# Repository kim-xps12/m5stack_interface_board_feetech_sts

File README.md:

# Feetech STS interface board for M5Stack

## About
M5StackからFeetech STSシリーズのシリアルサーボを操作するためのオリジナル基板です．KiCAD 7で設計しました．FE-URT-1([秋月リンク](https://akizukidenshi.com/catalog/g/gM-16295/))のUART機能のみを取り出して実装したため，同基板と比較して小型に収まっています．

## Appearance
**組み立て前**

**完成品**

## Usage
配線と動作の様子はこちら．
https://www.youtube.com/watch?v=_5FpvqL4ExI

動作確認用にM5Stack向けのサンプルコードをm5stack_uart_feetech_stsのリポジトリ（[リンク
](https://github.com/kim-xps12/m5stack_uart_feetech_sts/)）にて公開しています．よろしければご利用ください．

## schematics

## BOM
| Symbol | Model Number |URL, Values|
| --- | --- | --- |
| Q1  | 2SA1162GR<br> | [https://akizukidenshi.com/catalog/g/gI-02702/](https://akizukidenshi.com/catalog/g/gI-02702/)<br> |
| U1  | MAX3485ED<br> | [https://akizukidenshi.com/catalog/g/gI-16211/](https://akizukidenshi.com/catalog/g/gI-16211/)<br> |
| U2  | AP7333<br> | [https://akizukidenshi.com/catalog/g/gI-11360/](https://akizukidenshi.com/catalog/g/gI-11360/)<br> |
| J1  | JST B4B-PH-K-S(LF)(SN) | [https://www.sengoku.co.jp/mod/sgk\_cart/detail.php?code=4DK2-SDDB](https://www.sengoku.co.jp/mod/sgk_cart/detail.php?code=4DK2-SDDB)<br> |
| J2  | JST B2B-XH-A(LF)(SN) | [https://akizukidenshi.com/catalog/g/gC-12247/](https://akizukidenshi.com/catalog/g/gC-12247/)<br> |
| J3  | Molex 5267-03A-X | [https://www.sengoku.co.jp/mod/sgk\_cart/detail.php?code=EEHD-0HWA](https://www.sengoku.co.jp/mod/sgk_cart/detail.php?code=EEHD-0HWA)<br> |
| R   | 0608 inch / 1608 jis metric | R1=7.5k, R2=20k, R3=R4=2.2k |
| C   | 0608 inch / 1608 jis metric | C1=0.1 u, C2=C3=1u |

## Distribution
本基板（部品未実装）はboothで頒布中です．よろしければご利用ください．
https://b-sky-lab.booth.pm/items/5083992

## Reference
Feetechインターフェースボード回路図
https://akizukidenshi.com/download/ds/akizuki/feetech_digital_servo_20220729.pdf

## Disclaimer
MITライセンスでの公開です．本設計および頒布した基板において生じた一切の損害等について作者は責任を負いません．予めご了承ください．

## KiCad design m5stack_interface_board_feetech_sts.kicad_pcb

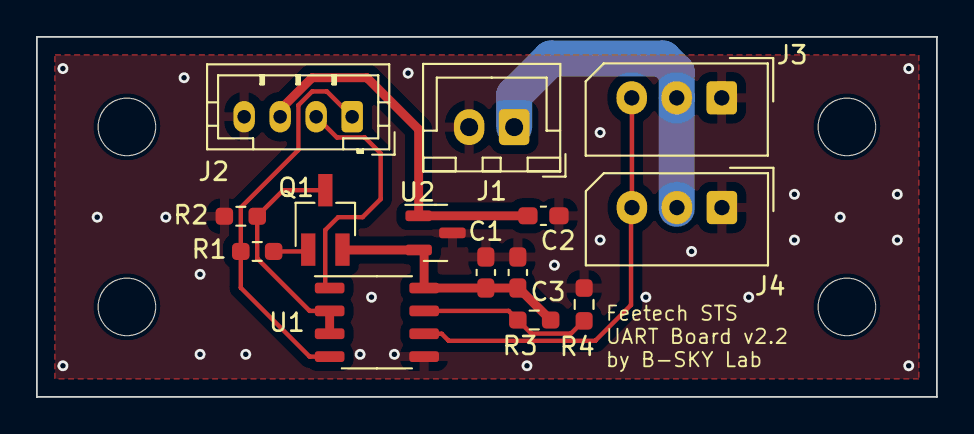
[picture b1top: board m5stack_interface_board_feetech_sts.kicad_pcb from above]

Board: 2 copper layers, 50.0 x 20.0 mm, 18 parts (0 on the bottom side), 10 nets.

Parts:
C1: 0.1u; C_0603_1608Metric_Pad1.08x0.95mm_HandSolder
C2, C3: 1u; C_0603_1608Metric_Pad1.08x0.95mm_HandSolder
J1: B2B-XH-A(LF)(SN); JST_XH_B2B-XH-A_1x02_P2.50mm_Vertical
J2: B4B-PH-K-S(LF)(SN); JST_PH_B4B-PH-K_1x04_P2.00mm_Vertical
J3, J4: 22035035; Molex_SPOX_5267-03A_1x03_P2.50mm_Vertical
MH1, MH2, MH3, MH4: MountingHole_3.2mm_M3
Q1: 2SA1162GR; SC-59_Handsoldering
R1: 7.5k; R_0603_1608Metric_Pad0.98x0.95mm_HandSolder
R2: 20k; R_0603_1608Metric_Pad0.98x0.95mm_HandSolder
R3, R4: 2.2k; R_0603_1608Metric_Pad0.98x0.95mm_HandSolder
U1: MAX3485; SOP-8_3.9x4.9mm_P1.27mm
U2: AP7333-33SAG; SOT-23

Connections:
+3.3V: C1.1, C3.1, Q1.2 (E), R3.2, U1.8 (VCC), U2.2 (VO)
+5V: C2.1, J2.3, U2.1 (VI)
/BAT: J1.1, J3.2, J4.2
/STS_RX: J2.2, U1.1 (RO)
/STS_TX: J2.1, R1.1, U1.4 (DI)
/signal: J3.3, J4.3, U1.6 (A)
GND: C1.2, C2.2, C3.2, J1.2, J2.4, J3.1, J4.1, R2.1, R4.1, U1.5 (GND), U2.3 (GND)
unnamed: Q1.1 (B), R1.2
unnamed: Q1.3 (C), R2.2, U1.2 (~RE), U1.3 (DE)
unnamed: R3.1, R4.2, U1.7 (B)

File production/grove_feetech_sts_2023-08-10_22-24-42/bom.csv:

Designator,Footprint,Quantity,Value,LCSC Part #
C1,1206,1,0.1u,
J1,JST_XH_S2B-XH-A_1x02_P2.50mm_Horizontal,1,BAT,
J2,Molex_SPOX_5268-03A_1x03_P2.50mm_Horizontal,1,Conn_01x03,
J3,JST_PH_S4B-PH-K_1x04_P2.00mm_Horizontal,1,Conn_01x04,
Q1,SC-59_Handsoldering,1,2SA1162,
R1,0603,1,7.5k,
R2,0603,1,20k,
"R3, R4",0603,2,2.2k,
U1,SOP-8_5.28x5.23mm_P1.27mm,1,MAX3485,
U2,SOT-23,1,AP7384-33SA,

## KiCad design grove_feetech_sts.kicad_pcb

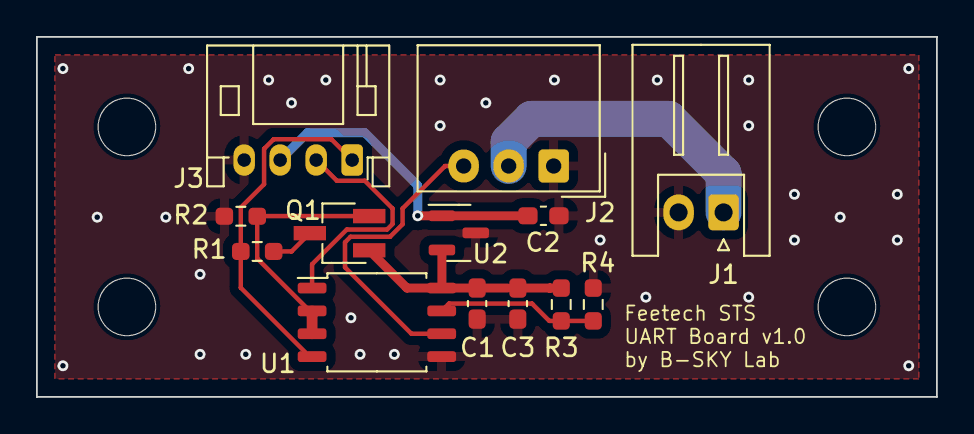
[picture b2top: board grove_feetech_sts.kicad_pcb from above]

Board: 2 copper layers, 50.0 x 20.0 mm, 17 parts (0 on the bottom side), 10 nets.

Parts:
C1: 0.1u; C_0603_1608Metric_Pad1.08x0.95mm_HandSolder
C2, C3: 1u; C_0603_1608Metric_Pad1.08x0.95mm_HandSolder
J1: BAT; JST_XH_S2B-XH-A_1x02_P2.50mm_Horizontal
J2: 0022057035; Molex_SPOX_5268-03A_1x03_P2.50mm_Horizontal
J3: Conn_01x04; JST_PH_S4B-PH-K_1x04_P2.00mm_Horizontal
MH1, MH2, MH3, MH4: MountingHole_3.2mm_M3
Q1: 2SA1162; SC-59_Handsoldering
R1: 7.5k; R_0603_1608Metric_Pad0.98x0.95mm_HandSolder
R2: 20k; R_0603_1608Metric_Pad0.98x0.95mm_HandSolder
R3, R4: 2.2k; R_0603_1608Metric_Pad0.98x0.95mm_HandSolder
U1: MAX3485; SOP-8_5.28x5.23mm_P1.27mm
U2: AP7384-33SA; SOT-23

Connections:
+3.3V: C1.1, C3.1, Q1.1 (E), R3.2, U1.8 (VCC), U2.2 (VO)
+5V: C2.1, J3.3, U2.1 (VI)
/BAT: J1.1, J2.2
/STS_RX: J3.2, U1.1 (RO)
/STS_TX: J3.1, R1.1, U1.4 (DI)
/signal: J2.3, U1.6 (A)
GND: C1.2, C2.2, C3.2, J1.2, J2.1, J3.4, R2.1, R4.1, U1.5 (GND), U2.3 (GND)
unnamed: Q1.3 (B), R1.2
unnamed: Q1.2 (C), R2.2, U1.2 (~RE), U1.3 (DE)
unnamed: R3.1, R4.2, U1.7 (B)

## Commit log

2023-08-10 1st commit, complete to desing v1.0
2023-09-10 complete to design ver. double molex
2023-09-10 add PCBWay's logo and URL
2023-09-10 complete to design ver. double molex (#1)
2023-09-10 Create LICENSE
2023-09-10 add image
2023-09-10 fix youtube link
2023-09-10 update README about KiCAD
